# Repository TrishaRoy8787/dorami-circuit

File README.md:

# Dorami circuit
This is my first ever circuit, but it wasn't too difficult.

I felt it to be a little difficult while creating the PCB from the schematic.

This is a circuit that lights up 2 LEDs. I have used a battery, 2 lights, a pushbutton, and a resistor.

## Screenshots

## BOM

| Part Name  | Quantity |
| ------------- | ------------- |
| Coin-sized Battery Holder  | x1  |
| LEDs  | x2  |
| 220 ohm resistor | x1 |
| 6mm tactile push buttons | x1 |

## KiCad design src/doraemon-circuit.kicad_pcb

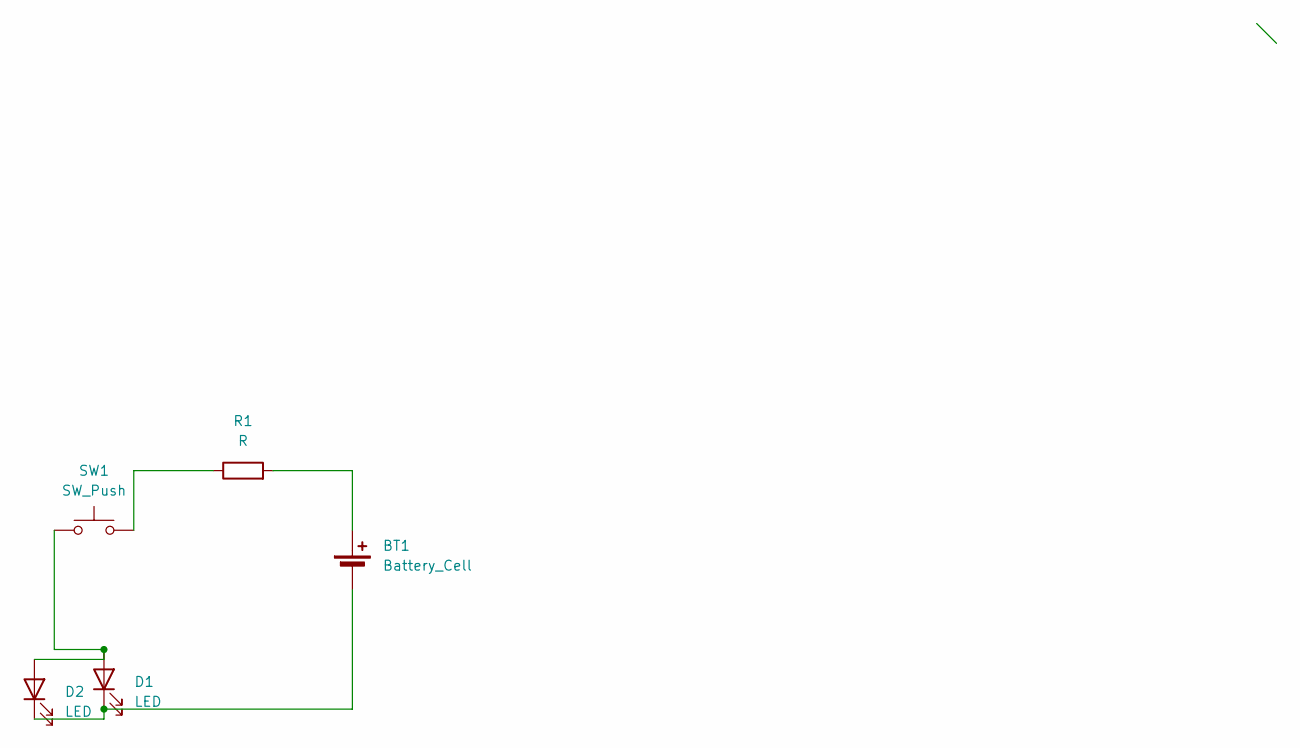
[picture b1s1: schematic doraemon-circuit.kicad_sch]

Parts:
BT1: Battery_Cell; BatteryHolder_Keystone_3034_1x20mm
D1, D2: LED; LED_D5.0mm
R1: R; R_Axial_DIN0207_L6.3mm_D2.5mm_P7.62mm_Horizontal
SW1: SW_Push; SW_PUSH_6mm

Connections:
unnamed: BT1.1 (+), R1.2
unnamed: BT1.2 (-), D1.1 (K), D2.1 (K)
unnamed: D1.2 (A), D2.2 (A), SW1.1
unnamed: R1.1, SW1.2

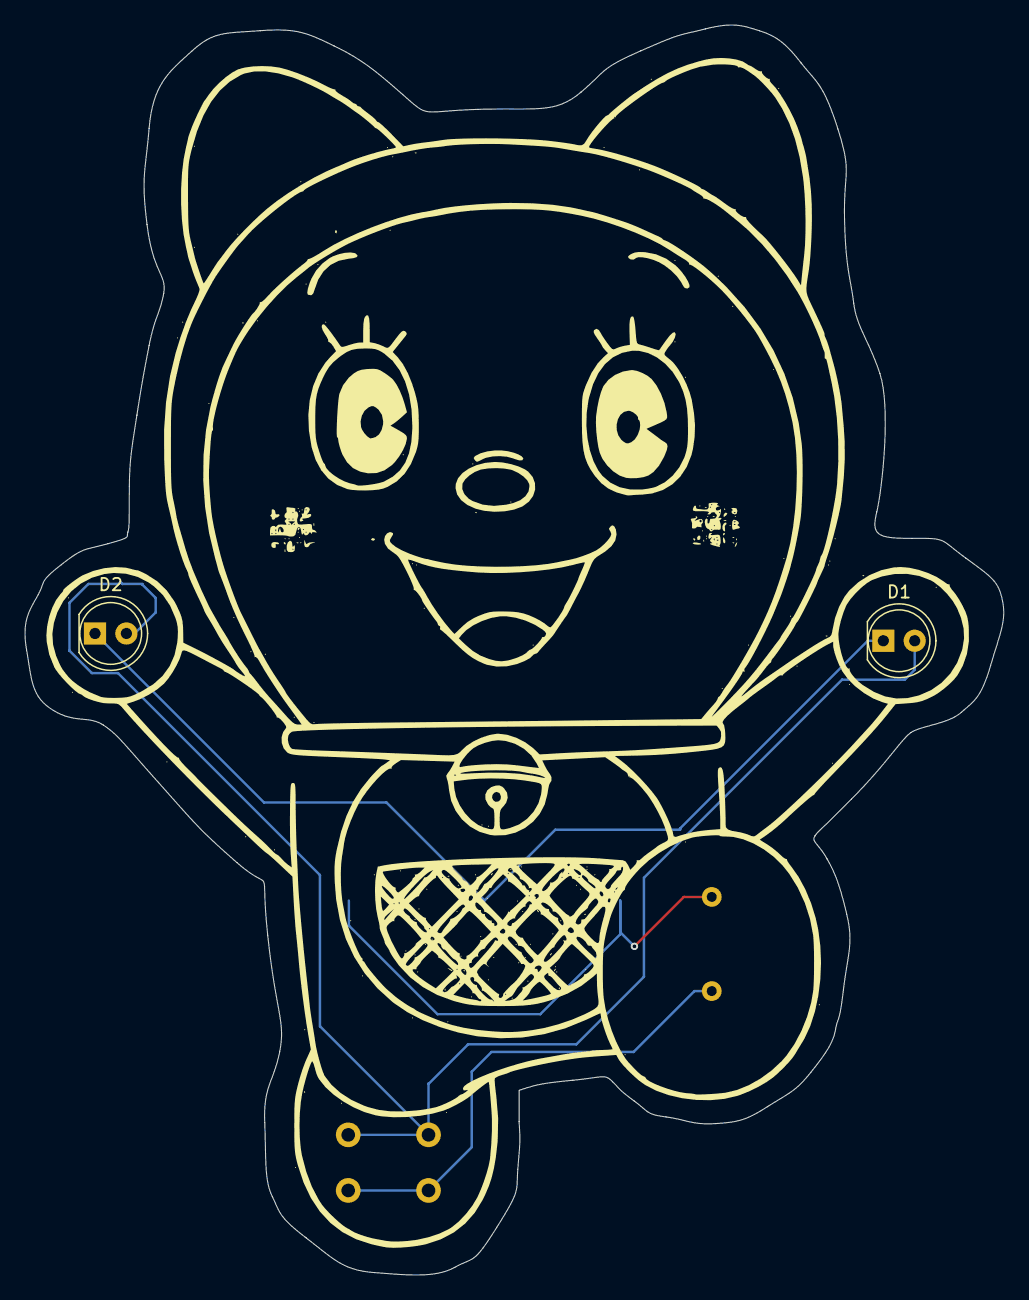
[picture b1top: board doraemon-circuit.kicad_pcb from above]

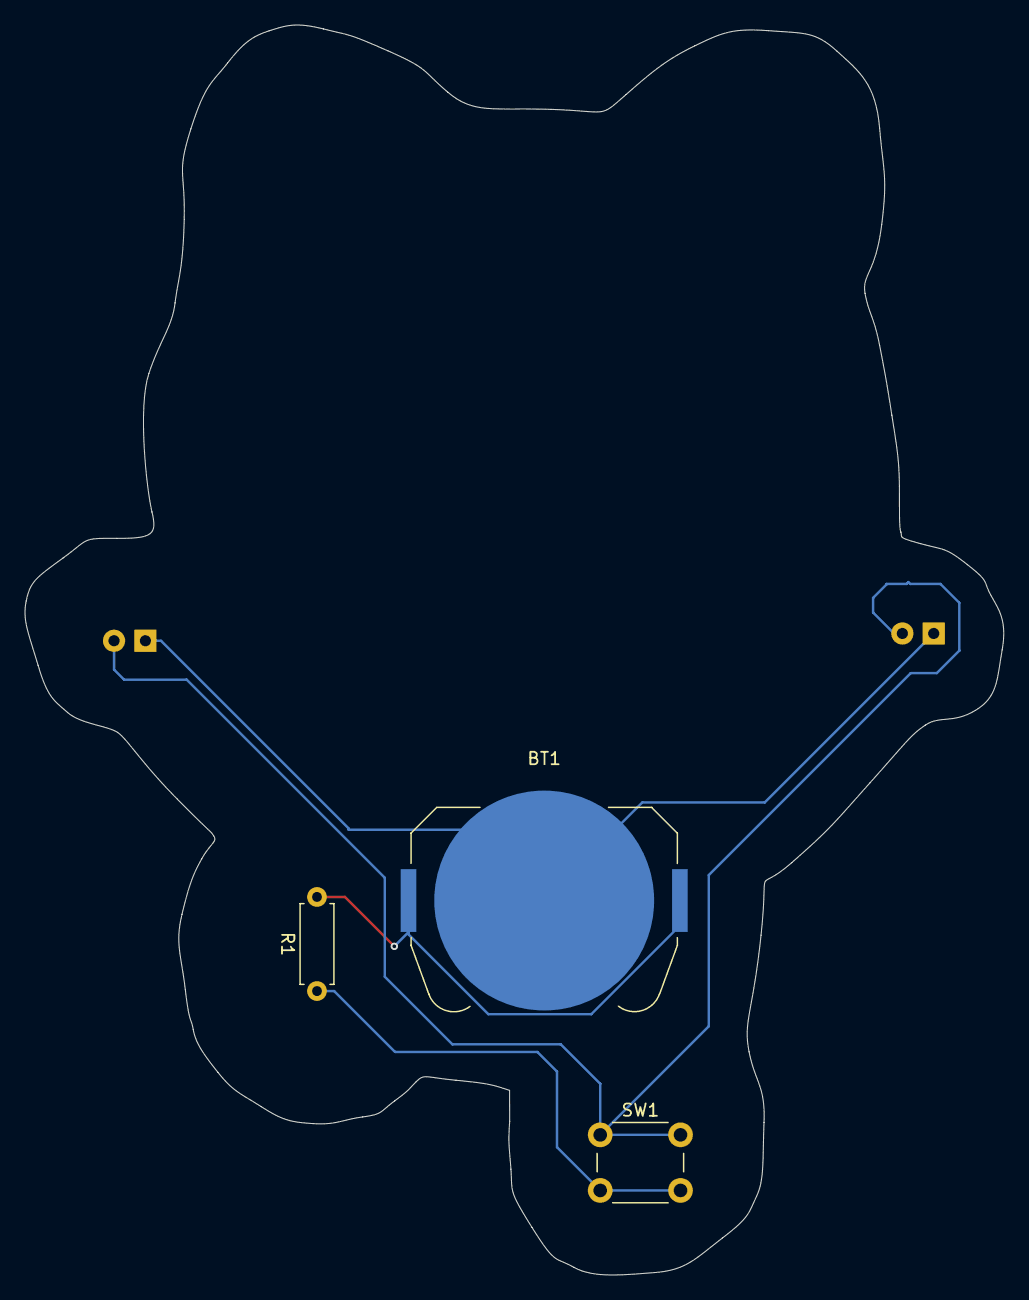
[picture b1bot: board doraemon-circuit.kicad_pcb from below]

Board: 2 copper layers, 79.2 x 101.2 mm, 5 parts (3 on the bottom side), 4 nets.

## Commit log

2025-05-28 Create test
2025-05-28 Added gerber files
2025-05-28 added images
2025-05-30 added Kicad files
